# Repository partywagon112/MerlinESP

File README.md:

ESP32-C6 Based Controller for my garage door. No serial. 
Main motivation is for a thread router or bluetooth proxy in the shed.

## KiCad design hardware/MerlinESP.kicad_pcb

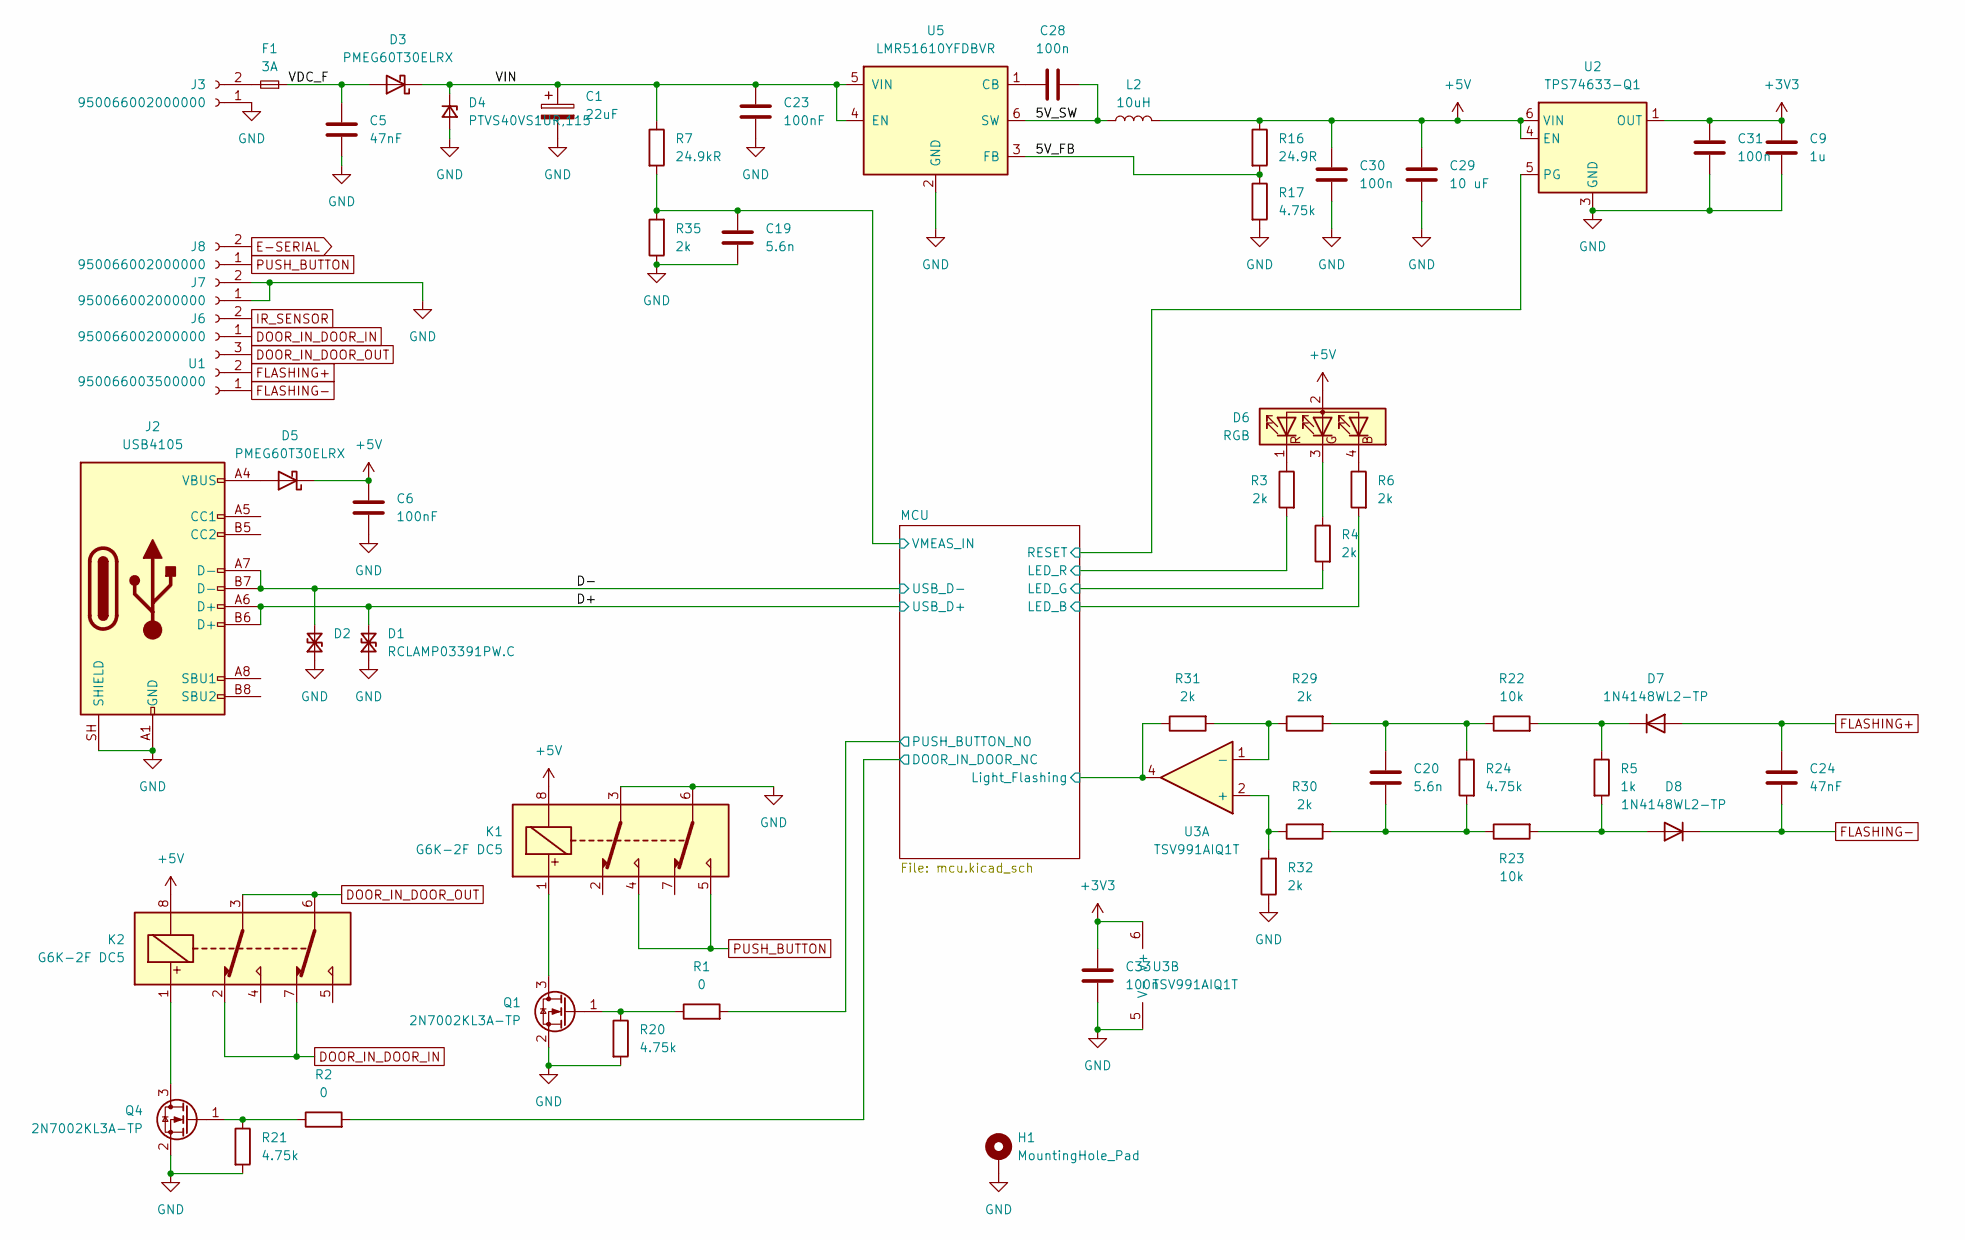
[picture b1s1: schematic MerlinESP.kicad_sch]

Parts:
C1: 22uF; CP_Elec_5x5.9; MPN EEE-FN1H220UR; DigiKey SPN 10-EEE-FN1H220URCT-ND
C5, C24: 47nF; C_0603_1608Metric; MPN CGA3E3X7S2A473K080AE; DigiKey SPN 445-173702-1-ND
C6, C23: 100nF; C_0603_1608Metric; MPN GCJ188R72A104KA01D; DigiKey SPN 490-13420-1-ND
C9: 1u; C_0603_1608Metric; MPN GRT188R61H105KE13D; DigiKey SPN 490-12330-1-ND
C19, C20: 5.6n; C_0402_1005Metric; MPN GCM155R71H562KA55D; DigiKey SPN 490-GCM155R71H562KA55DCT-ND
C28, C30, C31, C33: 100n; C_0402_1005Metric; MPN GCM155R71H104KE02J; DigiKey SPN 490-14514-1-ND
C29: 10 uF; C_0603_1608Metric; MPN GRT188R61E106ME13D; DigiKey SPN 490-12323-1-ND
D1, D2: RCLAMP03391PW.C; D_SOD-882; MPN RCLAMP03391PW.C; DigiKey SPN 600-RCLAMP03391PW.CCT-ND
D3, D5: PMEG60T30ELRX; Nexperia_CFP3_SOD-123W; MPN PMEG60T30ELRX; DigiKey SPN 1727-7806-1-ND
D4: PTVS40VS1UR,115; Nexperia_CFP3_SOD-123W; MPN PTVS40VS1UR,115; DigiKey SPN 1727-5873-1-ND
D6: RGB; LED_Kingbright_APFA3010_3x1.5mm_Horizontal; MPN APFA3010LSEEZGKQBKC; DigiKey SPN 754-1971-1-ND
D7, D8: 1N4148WL2-TP; D_0402_1005Metric; MPN 1N4148WL2-TP; DigiKey SPN 1N4148WL2-TPMSCT-ND
F1: 3A; Fuse_0805_2012Metric; MPN MFU0805FF03000P100; DigiKey SPN MFU08053.00CT-ND
H1: MountingHole_Pad; MountingHole_3.2mm_M3_ISO14580_Pad_TopBottom
J2: USB4105; USB_C_Receptacle_GCT_USB4105-xx-A_16P_TopMnt_Horizontal; MPN USB4105-GF-A; DigiKey SPN 2073-USB4105-GF-ACT-ND
J3, J6, J7, J8: 950066002000000; Wurth_TBL_0066_x2; MPN 950066002000000; DigiKey SPN 732-950066002000000-ND
K1, K2: G6K-2F DC5; Relay_DPDT_Omron_G6K-2F; MPN G6K-2F DC5; DigiKey SPN Z112-ND
L2: 10uH; L_1008_2520Metric; MPN SRN2510BTA-100M; DigiKey SPN 118-SRN2510BTA-100MCT-ND
Q1, Q4: 2N7002KL3A-TP; Diodes_DFN1006-3; MPN 2N7002KL3A-TP; DigiKey SPN 353-2N7002KL3A-TPCT-ND
R1, R2: 0; R_0402_1005Metric; MPN CR0402AJ/-000GLF; DigiKey SPN 118-CR0402AJ/-000GLFCT-ND
R3, R4, R6, R29, R30, R31, R32, R35: 2k; R_0402_1005Metric; MPN CR0402AFX-2001GAS; DigiKey SPN 118-CR0402AFX-2001GASCT-ND
R5: 1k; R_0603_1608Metric; MPN CR0603AFX-1001ELF; DigiKey SPN 118-CR0603AFX-1001ELFCT-ND
R7: 24.9kR; R_0603_1608Metric; MPN RNCP0603FTD24K9; DigiKey SPN RNCP0603FTD24K9CT-ND
R16: 24.9R; R_0402_1005Metric; MPN ERJ-2RKF2492X; DigiKey SPN P24.9KLCT-ND
R17, R20, R21, R24: 4.75k; R_0402_1005Metric; MPN CR0402AFX-4751GAS; DigiKey SPN CR0402AFX-4751GASCT-ND
R22, R23: 10k; R_0603_1608Metric; MPN CR0603-FX-1002ELF; DigiKey SPN CR0603-FX-1002ELFCT-ND
U1: 950066003500000; Wurth_TBL_0066_x3; MPN 950066003500000; DigiKey SPN 732-950066003500000-ND
U2: TPS74633-Q1; WSON-6-1EP_2x2mm_P0.65mm_EP1x1.6mm; MPN TPS74633PCQWDRVRQ1; DigiKey SPN 296-TPS74633PCQWDRVRQ1CT-ND
U3: TSV991AIQ1T; DFN-6_1.6x1.3mm_P0.4mm; MPN TSV991AIQ1T; DigiKey SPN 497-15999-1-ND
U5: LMR51610YFDBVR; SOT-23-6; MPN LMR51610YFDBVR; DigiKey SPN 296-LMR51610YFDBVRCT-ND

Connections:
+3V3: C9.1, C31.1, C33.1, U2.1 (OUT), U3.6 (V+); also elsewhere on the board
+5V: C6.1, C29.1, C30.1, D5.1 (K), D6.2 (A), K1.8, K2.8, L2.2, R16.1, U2.4 (EN), U2.6 (VIN)
/5V_FB: R16.2, R17.1, U5.3 (FB)
/5V_SW: C28.2, L2.1, U5.6 (SW)
/D+: D1.2 (A2), J2.A6 (D+), J2.B6 (D+); also elsewhere on the board
/D-: D2.2 (A2), J2.A7 (D-), J2.B7 (D-); also elsewhere on the board
/MCU/DOOR_IN_DOOR_NC: R2.2; also elsewhere on the board
/MCU/LED_B: R6.2; also elsewhere on the board
/MCU/LED_G: R4.2; also elsewhere on the board
/MCU/LED_R: R3.2; also elsewhere on the board
/MCU/Light_Flashing: R31.1, U3.4; also elsewhere on the board
/MCU/PUSH_BUTTON_NO: R1.2; also elsewhere on the board
/MCU/VMEAS_IN: C19.1, R7.2, R35.2; also elsewhere on the board
/MCU/~RST: U2.5 (PG); also elsewhere on the board
/VDC_F: C5.1, D3.2 (A), F1.1
/VIN: C1.1, C23.1, D3.1 (K), D4.1 (K), R7.1, U5.4 (EN), U5.5 (VIN)
DOOR_IN_DOOR_IN: J6.1, K2.2, K2.7
DOOR_IN_DOOR_OUT: K2.3, K2.6, U1.3
E-SERIAL: J8.2
FLASHING+: C24.1, D7.2 (A), U1.2
FLASHING-: C24.2, D8.1 (K), U1.1
GND: C1.2, C5.2, C6.2, C9.2, C19.2, C23.2, C29.2, C30.2, C31.2, C33.2, D1.1 (A1), D2.1 (A1), D4.2 (A), H1.1 (1_1), J2.A1 (GND), J2.A12 (GND), J2.B1 (GND), J2.B12 (GND), J2.SH (SHIELD), J3.1, J7.1, J7.2, K1.3, K1.6, Q1.2 (S), Q4.2 (S), R17.2, R20.2, R21.2, R32.1, R35.1, U2.3 (GND), U2.7 (GND), U3.5 (V-), U5.2 (GND); also elsewhere on the board
IR_SENSOR: J6.2
unnamed: C20.1, R22.1, R24.1, R29.2
unnamed: C20.2, R23.1, R24.2, R30.2
unnamed: D5.2 (A), J2.A4 (VBUS), J2.A9 (VBUS), J2.B4 (VBUS), J2.B9 (VBUS)
unnamed: D6.4 (B), R6.1
unnamed: D6.3 (G), R4.1
unnamed: D6.1 (R), R3.1
unnamed: D7.1 (K), R5.1, R22.2
unnamed: D8.2 (A), R5.2, R23.2
unnamed: F1.2, J3.2
unnamed: K1.1, Q1.3 (D)
unnamed: Q1.1 (G), R1.1, R20.1
unnamed: K2.1, Q4.3 (D)
unnamed: Q4.1 (G), R2.1, R21.1
unnamed: R30.1, R32.2, U3.2 (+)
unnamed: R29.1, R31.2, U3.1 (-)
unnamed: C28.1, U5.1 (CB)
PUSH_BUTTON: J8.1, K1.4, K1.5

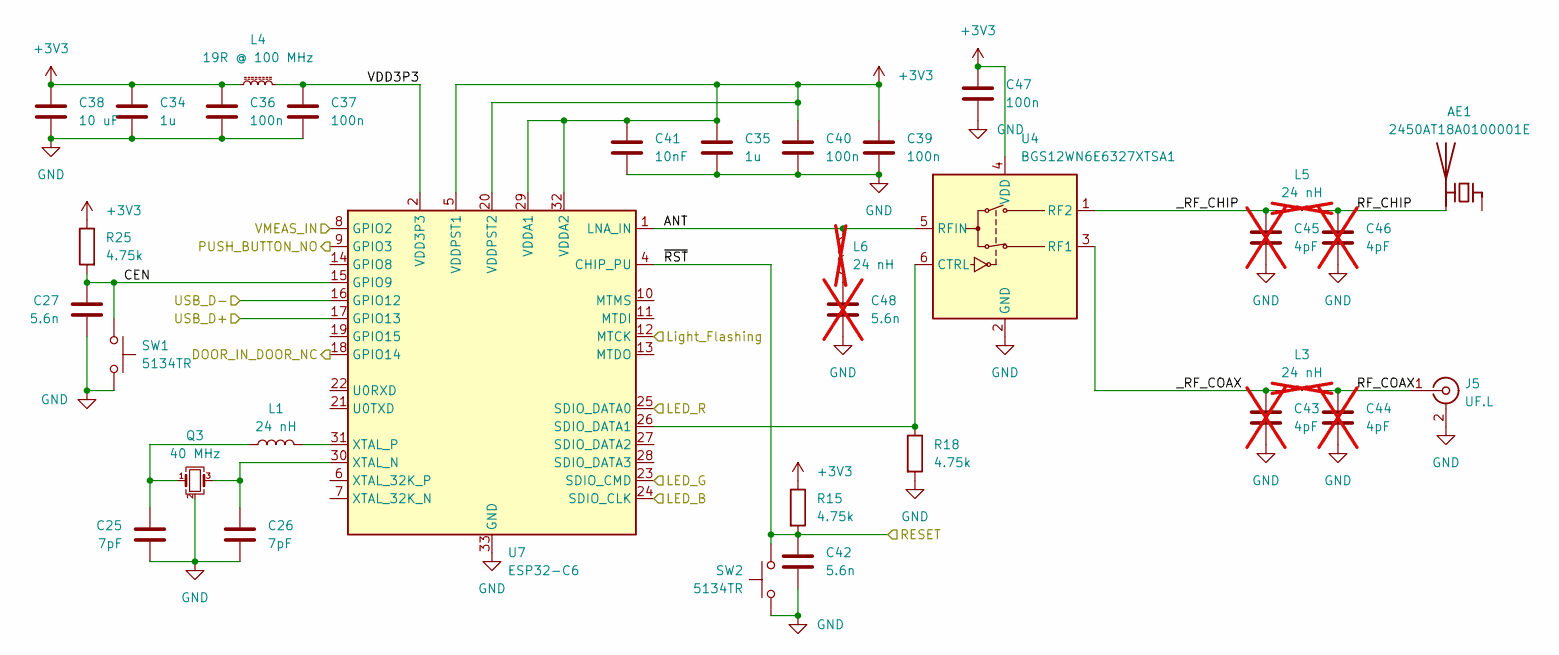
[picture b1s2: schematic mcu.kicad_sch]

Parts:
AE1: 2450AT18A0100001E; Johanson_2450AT18x100; MPN 2450AT18A0100001E; DigiKey SPN 712-2450AT18A0100001ECT-ND
C25, C26: 7pF; C_0402_1005Metric; MPN GCM1555C1H7R0BA16D; DigiKey SPN 490-GCM1555C1H7R0BA16DCT-ND
C27, C42: 5.6n; C_0402_1005Metric; MPN GCM155R71H562KA55D; DigiKey SPN 490-GCM155R71H562KA55DCT-ND
C34, C35: 1u; C_0603_1608Metric; MPN GRT188R61H105KE13D; DigiKey SPN 490-12330-1-ND
C36, C37, C39, C40, C47: 100n; C_0402_1005Metric; MPN GCM155R71H104KE02J; DigiKey SPN 490-14514-1-ND
C38: 10 uF; C_0603_1608Metric; MPN GRT188R61E106ME13D; DigiKey SPN 490-12323-1-ND
C41: 10nF; C_0402_1005Metric; MPN GCM155R71H103KA55D; DigiKey SPN 490-4762-1-ND
C43, C44, C45, C46: 4pF; C_0402_1005Metric; MPN GCM1555C1H4R0BA16D; DigiKey SPN 490-GCM1555C1H4R0BA16DCT-ND; not fitted
C48: 5.6n; C_0402_1005Metric; MPN GCM155R71H562KA55D; DigiKey SPN 490-GCM155R71H562KA55DCT-ND; not fitted
J5: UF.L; U.FL_Hirose_U.FL-R-SMT-1_Vertical; MPN U.FL-R-SMT(10); DigiKey SPN H9161CT-ND
L1: 24 nH; L_0402_1005Metric; MPN MLG1005S24NJTD25; DigiKey SPN 445-16275-1-ND
L3, L5, L6: 24 nH; L_0402_1005Metric; MPN MLG1005S24NJTD25; DigiKey SPN 445-16275-1-ND; not fitted
L4: 19R @ 100 MHz; L_0402_1005Metric; MPN LI0402E190R-10; DigiKey SPN 240-LI0402E190R-10CT-ND
Q3: 40 MHz; Crystal_SMD_2016-4Pin_2.0x1.6mm; MPN XTL501100-M118-207; DigiKey SPN 3994-XTL501100-M118-207CT-ND
R15, R18, R25: 4.75k; R_0402_1005Metric; MPN CR0402AFX-4751GAS; DigiKey SPN CR0402AFX-4751GASCT-ND
SW1, SW2: 5134TR; Keystone_5134TR; MPN 5134TR; DigiKey SPN 36-5134CT-ND
U4: BGS12WN6E6327XTSA1; Infineon_PG-TSNP-6-10_0.7x1.1mm_0.7x1.1mm_P0.4mm; MPN BGS12WN6E6327XTSA1; DigiKey SPN 448-BGS12WN6E6327XTSA1CT-ND
U7: ESP32-C6; QFN-32-1EP_5x5mm_P0.5mm_EP3.7x3.7mm; MPN ESP32-C6FH4; DigiKey SPN 1904-ESP32-C6FH4CT-ND

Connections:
+3V3: C34.1, C35.1, C36.1, C38.1, C39.1, C40.1, C41.1, C47.1, L4.1, R15.1, R25.1, U4.4 (VDD), U7.5 (VDDPST1), U7.20 (VDDPST2), U7.29 (VDDA1), U7.32 (VDDA2); also elsewhere on the board
/D+: U7.17 (GPIO13); also elsewhere on the board
/D-: U7.16 (GPIO12); also elsewhere on the board
/MCU/ANT: L6.2, U4.5 (RFIN), U7.1 (LNA_IN)
/MCU/CEN: C27.1, R25.2, SW1.2, U7.15 (GPIO9)
/MCU/DOOR_IN_DOOR_NC: U7.18 (GPIO14); also elsewhere on the board
/MCU/LED_B: U7.24 (SDIO_CLK); also elsewhere on the board
/MCU/LED_G: U7.23 (SDIO_CMD); also elsewhere on the board
/MCU/LED_R: U7.25 (SDIO_DATA0); also elsewhere on the board
/MCU/Light_Flashing: U7.12 (MTCK); also elsewhere on the board
/MCU/PUSH_BUTTON_NO: U7.9 (GPIO3); also elsewhere on the board
/MCU/RF_CHIP: AE1.2 (PCB_Trace_2), C46.1, L5.2
/MCU/RF_COAX: C44.1, J5.1 (In), L3.2
/MCU/VMEAS_IN: U7.8 (GPIO2); also elsewhere on the board
/MCU/_RF_CHIP: C45.1, L5.1, U4.1 (RF2)
/MCU/_RF_COAX: C43.1, L3.1, U4.3 (RF1)
/MCU/~RST: C42.1, R15.2, SW2.2, U7.4 (CHIP_PU); also elsewhere on the board
GND: C25.2, C26.2, C27.2, C34.2, C35.2, C36.2, C37.2, C38.2, C39.2, C40.2, C41.2, C42.2, C43.2, C44.2, C45.2, C46.2, C47.2, C48.2, J5.2 (Ext), Q3.2 (G), Q3.4 (G), R18.2, SW1.1, SW2.1, U4.2 (GND), U7.33 (GND); also elsewhere on the board
unnamed: C25.1, L1.1, Q3.1
unnamed: C48.1, L6.1
unnamed: R18.1, U4.6 (CTRL), U7.26 (SDIO_DATA1)
unnamed: C26.1, Q3.3, U7.30 (XTAL_N)
unnamed: L1.2, U7.31 (XTAL_P)
VDD3P3: C37.1, L4.2, U7.2 (VDD3P3), U7.3 (VDD3P3)

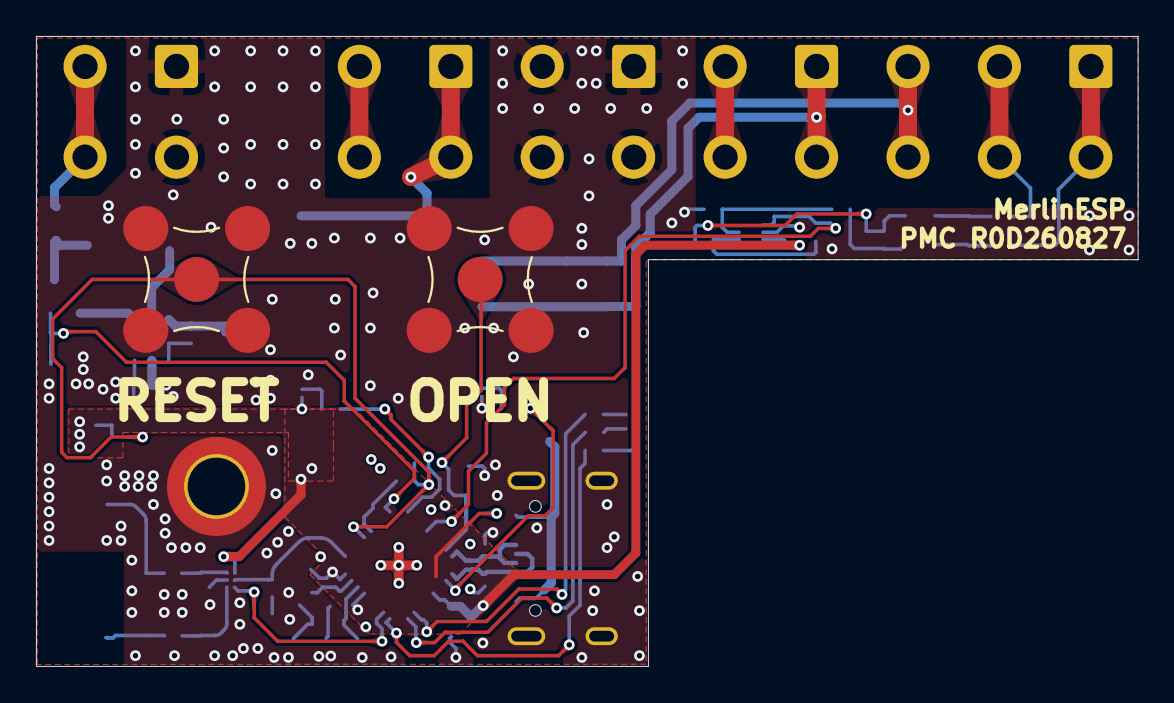
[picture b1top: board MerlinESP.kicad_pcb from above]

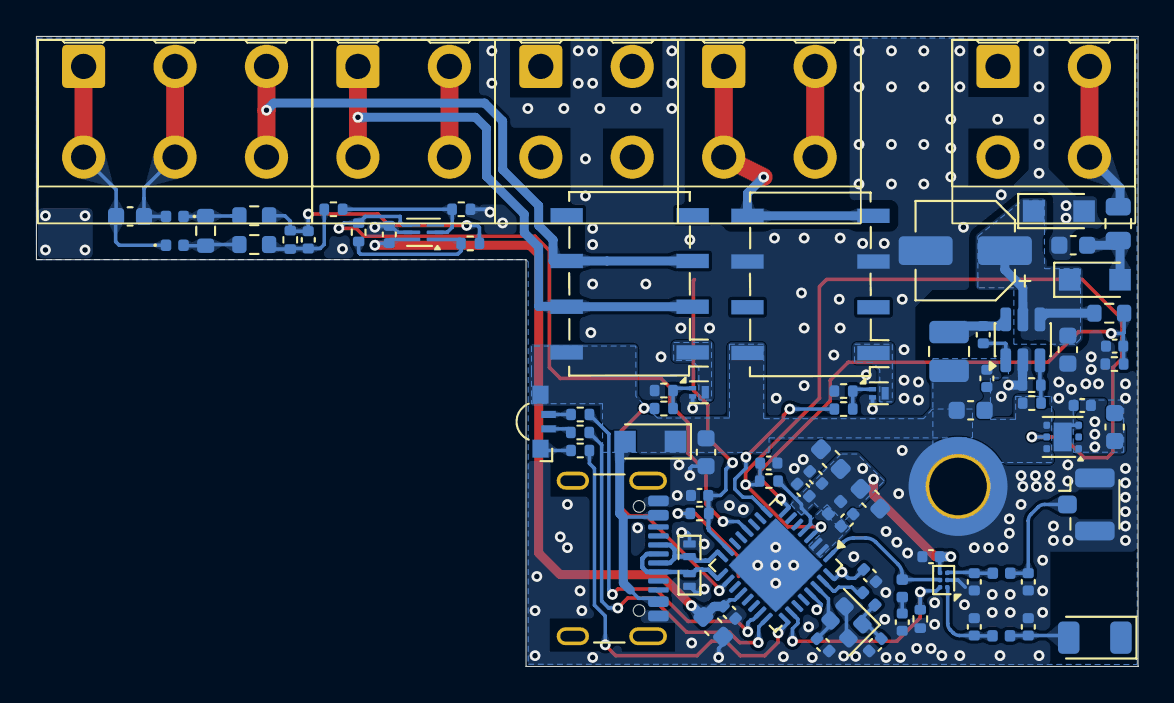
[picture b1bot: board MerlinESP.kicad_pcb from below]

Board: 4 copper layers, 61.2 x 35.0 mm, 89 parts (86 on the bottom side), 50 nets.
